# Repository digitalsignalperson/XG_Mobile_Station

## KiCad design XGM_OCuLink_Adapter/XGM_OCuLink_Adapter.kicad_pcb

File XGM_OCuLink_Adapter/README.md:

XGM to OCuLink Adapter
======================
A 33 x 18 mm board that plugs straight into the XG Mobile port of an ROG Flow / ROG Ally and presents a standard OCuLink 4i (SFF-8612) host port, so any off-the-shelf OCuLink eGPU dock can be used with a normal OCuLink cable.

**Status: untested design, revision 0.1. Do not order boards before working through [Before you order](#before-you-order).** The schematic is complete and checked; the board layout depends on the dimensions of a connector that had to be estimated from photos.

| Top copper | Bottom copper |
|---|---|
|  |  |

The XGM plug solders onto the lower edge, the OCuLink receptacle sits top right, the MCU top left.

## How it works
The XGM port is PCIe x8 plus a handful of sideband signals plus a USB-C port ([pinout](../Docs/Connector.md)). OCuLink 4i is PCIe x4 plus reference clock and reset. So the adapter has three jobs:

1. **Pass lanes 0-3 and the reference clock straight through.** No AC coupling capacitors are needed: PCIe puts them at each transmitter, so they already exist on the laptop motherboard and on the graphics card. Lanes 4-7 are left open and the host trains the link down to x4.
2. **Answer the handshake.** The laptop's embedded controller will not switch the PCIe mux over until a dock identifies itself over the sideband pins and the SMBus ([details](../Docs/MCU.md)). This is done by the same STM32F030C8T6, on the same pins, as the Lite dock, so the existing `XG_Mobile_Dock_MCU` firmware runs unmodified.
3. **Power itself.** OCuLink carries no power and there is no ATX supply here. A 5.1 kΩ resistor on CC1 makes the adapter look like a USB-C device, so the port's own USB-C half supplies 5 V on VBUS. A 3.3 V LDO feeds the MCU (about 10 mA).

`GPU_RST#` reaches the dock as OCuLink `PERST#` through the MCU, exactly as on the Lite dock. The other OCuLink sidebands (`CWAKE#`, `CPRSNT#`, the 2-wire bus, the 3.3 V / 5 V cable power pins) are not connected.

### About "you need redrivers"
A redriver is an amplifier that restores a PCIe signal which has been weakened by a long path. The comment that an adapter needs them assumed the adapter sits at the end of the ASUS XGM cable, so the signal would cross that cable *and* an OCuLink cable. This design removes the ASUS cable entirely: the plug is soldered to the board and the trace length from plug to OCuLink connector is about 10 mm. The signal path is laptop, 10 mm of board, one OCuLink cable, dock. That is comparable to the stock setup, so this revision is passive.

Expect PCIe 3.0 to work. PCIe 4.0 is plausible on a ROG Flow (which has redrivers on its motherboard) with a short, good cable, and less likely on a ROG Ally (which has none). If the link is unstable, use a shorter cable or let it fall back to 3.0, see the troubleshooting section of the [main README](../README.md).

## The connector problem
The male XGM plug is not a catalogue part. Parts stores only sell the receptacle that sits in the laptop. The only source is an ASUS XG Mobile cable ([part 14017-00810700](https://www.a-accessories.com/asus-connection-cable-62505-79153.htm), about $129, or a cable from a dead XG Mobile): open the cable head and desolder the plug from the small PCB inside. [These photos](../Docs/Diary.md#pin-mapping) show what that PCB looks like. The plug straddles the board edge, with rows A and C soldered on one face and rows B and D on the other.

Because of that, the plug footprint (`lib/XGM_OCuLink.pretty/XGM_Plug_Straddle.kicad_mod`) is an **estimate** made from those photos. The values that were guessed are at the top of `gen/make_fp.py`:

| Parameter  | Guess   | Meaning                                         |
|------------|---------|-------------------------------------------------|
| `pitch`    | 0.5 mm  | contact pitch, both sections                    |
| `pad_w`    | 0.28 mm | solder pad width                                |
| `pad_len`  | 1.4 mm  | solder pad length                               |
| `pad_edge` | 0.3 mm  | board edge to start of pad                      |
| `usb_gap`  | 4.1 mm  | centre of C31 to centre of A1                   |
| `shell_*`  |         | size and position of the shell tabs             |
| `board_t`  | 0.8 mm  | PCB thickness the plug is made to straddle      |

The outline of the board around the plug (notches for the plastic posts visible in the photos) is not modelled at all.

## Before you order
1. Get the plug. Measure it and the original cable-head PCB with calipers: every value in the table above, plus the cut-outs in the board edge.
2. Confirm with a multimeter that row D sits under row C with the same numbering (D1 under C1) and that B12 sits under A1. The original PCB has these labels on its silkscreen.
3. Put the measured values into `gen/make_fp.py` and regenerate (see below). The PCIe routing is computed from these numbers and follows them. Add the edge cut-outs in KiCad.
4. Check the chosen OCuLink receptacle against the footprint. It was drawn for the Amphenol G14A421211112HR; other SFF-8612 right-angle receptacles differ.
5. Enter the stack-up of your PCB fab into its impedance calculator and adjust `W_PAIR` / `GAP_PAIR` in `gen/make_pcb.py` for 85 Ω differential. The current 0.16 mm / 0.15 mm is an approximation for a 0.1 mm prepreg (JLC04081H-3313).
6. Run DRC in KiCad.

Things that can only be found out with a board in hand:

* Whether the port supplies VBUS early enough at boot for the MCU to answer the BIOS check. The `5V` pad (TP7) accepts external 5 V if it does not.
* Whether the plug stays seated. The original cable head latches into the laptop; this board is held by friction and the solder joints of the plug shell, with a stiff OCuLink cable hanging off it. A printed shell is advisable.
* Whether your dock powers the GPU up on its own. Docks that expect 3.3 V on the OCuLink cable power pins to switch on will need their manual power switch.

## Using it
Flash `XG_Mobile_Dock_MCU.bin` through the row of pads on the bottom side (`DIO`, `CLK`, `GND`, `3V3`), as described in the [main README](../README.md#stm32-mcu). `TX` is the debug log at 115200 baud.

The firmware's cable-lock input is left floating, which reads as "locked", so the adapter announces itself as soon as it is plugged in. Bridging `JP1` reads as "unlocked".

* White LED: connected and locked. Red LED: the host has enabled the eGPU.
* Windows: install [XGMDriver](../README.md#install-xgmdriver).
* Linux: the `asus-nb-wmi` driver exposes `egpu_enable` under `/sys/devices/platform/asus-nb-wmi/` (also reachable through `asusctl`). Write `1` to it after plugging in, then reboot or rescan the PCI bus.
* The USB-C half of the port is used up by the adapter. A ROG Flow can charge from its other USB-C port; a first-generation ROG Ally has no other port and cannot charge while the adapter is in.

## Files
| Path                                | Contents                                                  |
|-------------------------------------|-----------------------------------------------------------|
| `XGM_OCuLink_Adapter.kicad_sch`     | Schematic (generated: every pin carries a net label)      |
| `XGM_OCuLink_Adapter.kicad_pcb`     | 4-layer board, 0.8 mm, inner layers are solid ground      |
| `lib/`                              | Symbols and footprints used by the project                |
| `gen/design.py`                     | Parts, pins and nets. The single source of truth          |
| `gen/make_fp.py`                    | Plug footprint, with the estimated dimensions             |
| `gen/make_sch.py`                   | Writes the symbol library and the schematic               |
| `gen/make_pcb.py`, `gen/router.py`  | Placement, PCIe routing by construction, low-speed router |

To regenerate everything (KiCad 9 or later, with its Python module, numpy and scipy):

```
cd gen
./make_fp.py && ./make_sch.py
kicad-cli sch export netlist --format kicadsexpr -o /tmp/adapter.net ../XGM_OCuLink_Adapter.kicad_sch
./make_pcb.py /tmp/adapter.net      # takes about two minutes
```

The PCIe pairs are placed by formula, so their geometry is exact and repeatable. The low-speed nets are placed by a simple grid router: they are electrically correct and pass DRC, but they are not pretty, and are worth tidying by hand once the footprint is final.

## Layout notes
* TX pairs run on the top layer from plug row C to OCuLink row B. RX pairs drop to the bottom layer, pass under row B and come back up between the two pad rows to reach row A. Every ground pin next to a pair has its own via into the planes, at both connectors.
* Polarity and lane order are preserved end to end.
* The reference clock starts on the bottom face (row D) and has to cross lane 2 to reach the middle of the OCuLink connector. It does so on the bottom layer while RX2 is still on the top layer, so no pair crosses a gap in its ground plane.
* `PERST#` runs around the front of the OCuLink connector instead of across the pairs.

## Sources
* OCuLink pin assignment: SFF-9402 Rev 1.1, Table 7-1, root side.
* OCuLink footprint: Antmicro [oculink-pcie-adapter](https://github.com/antmicro/oculink-pcie-adapter) (Apache-2.0).

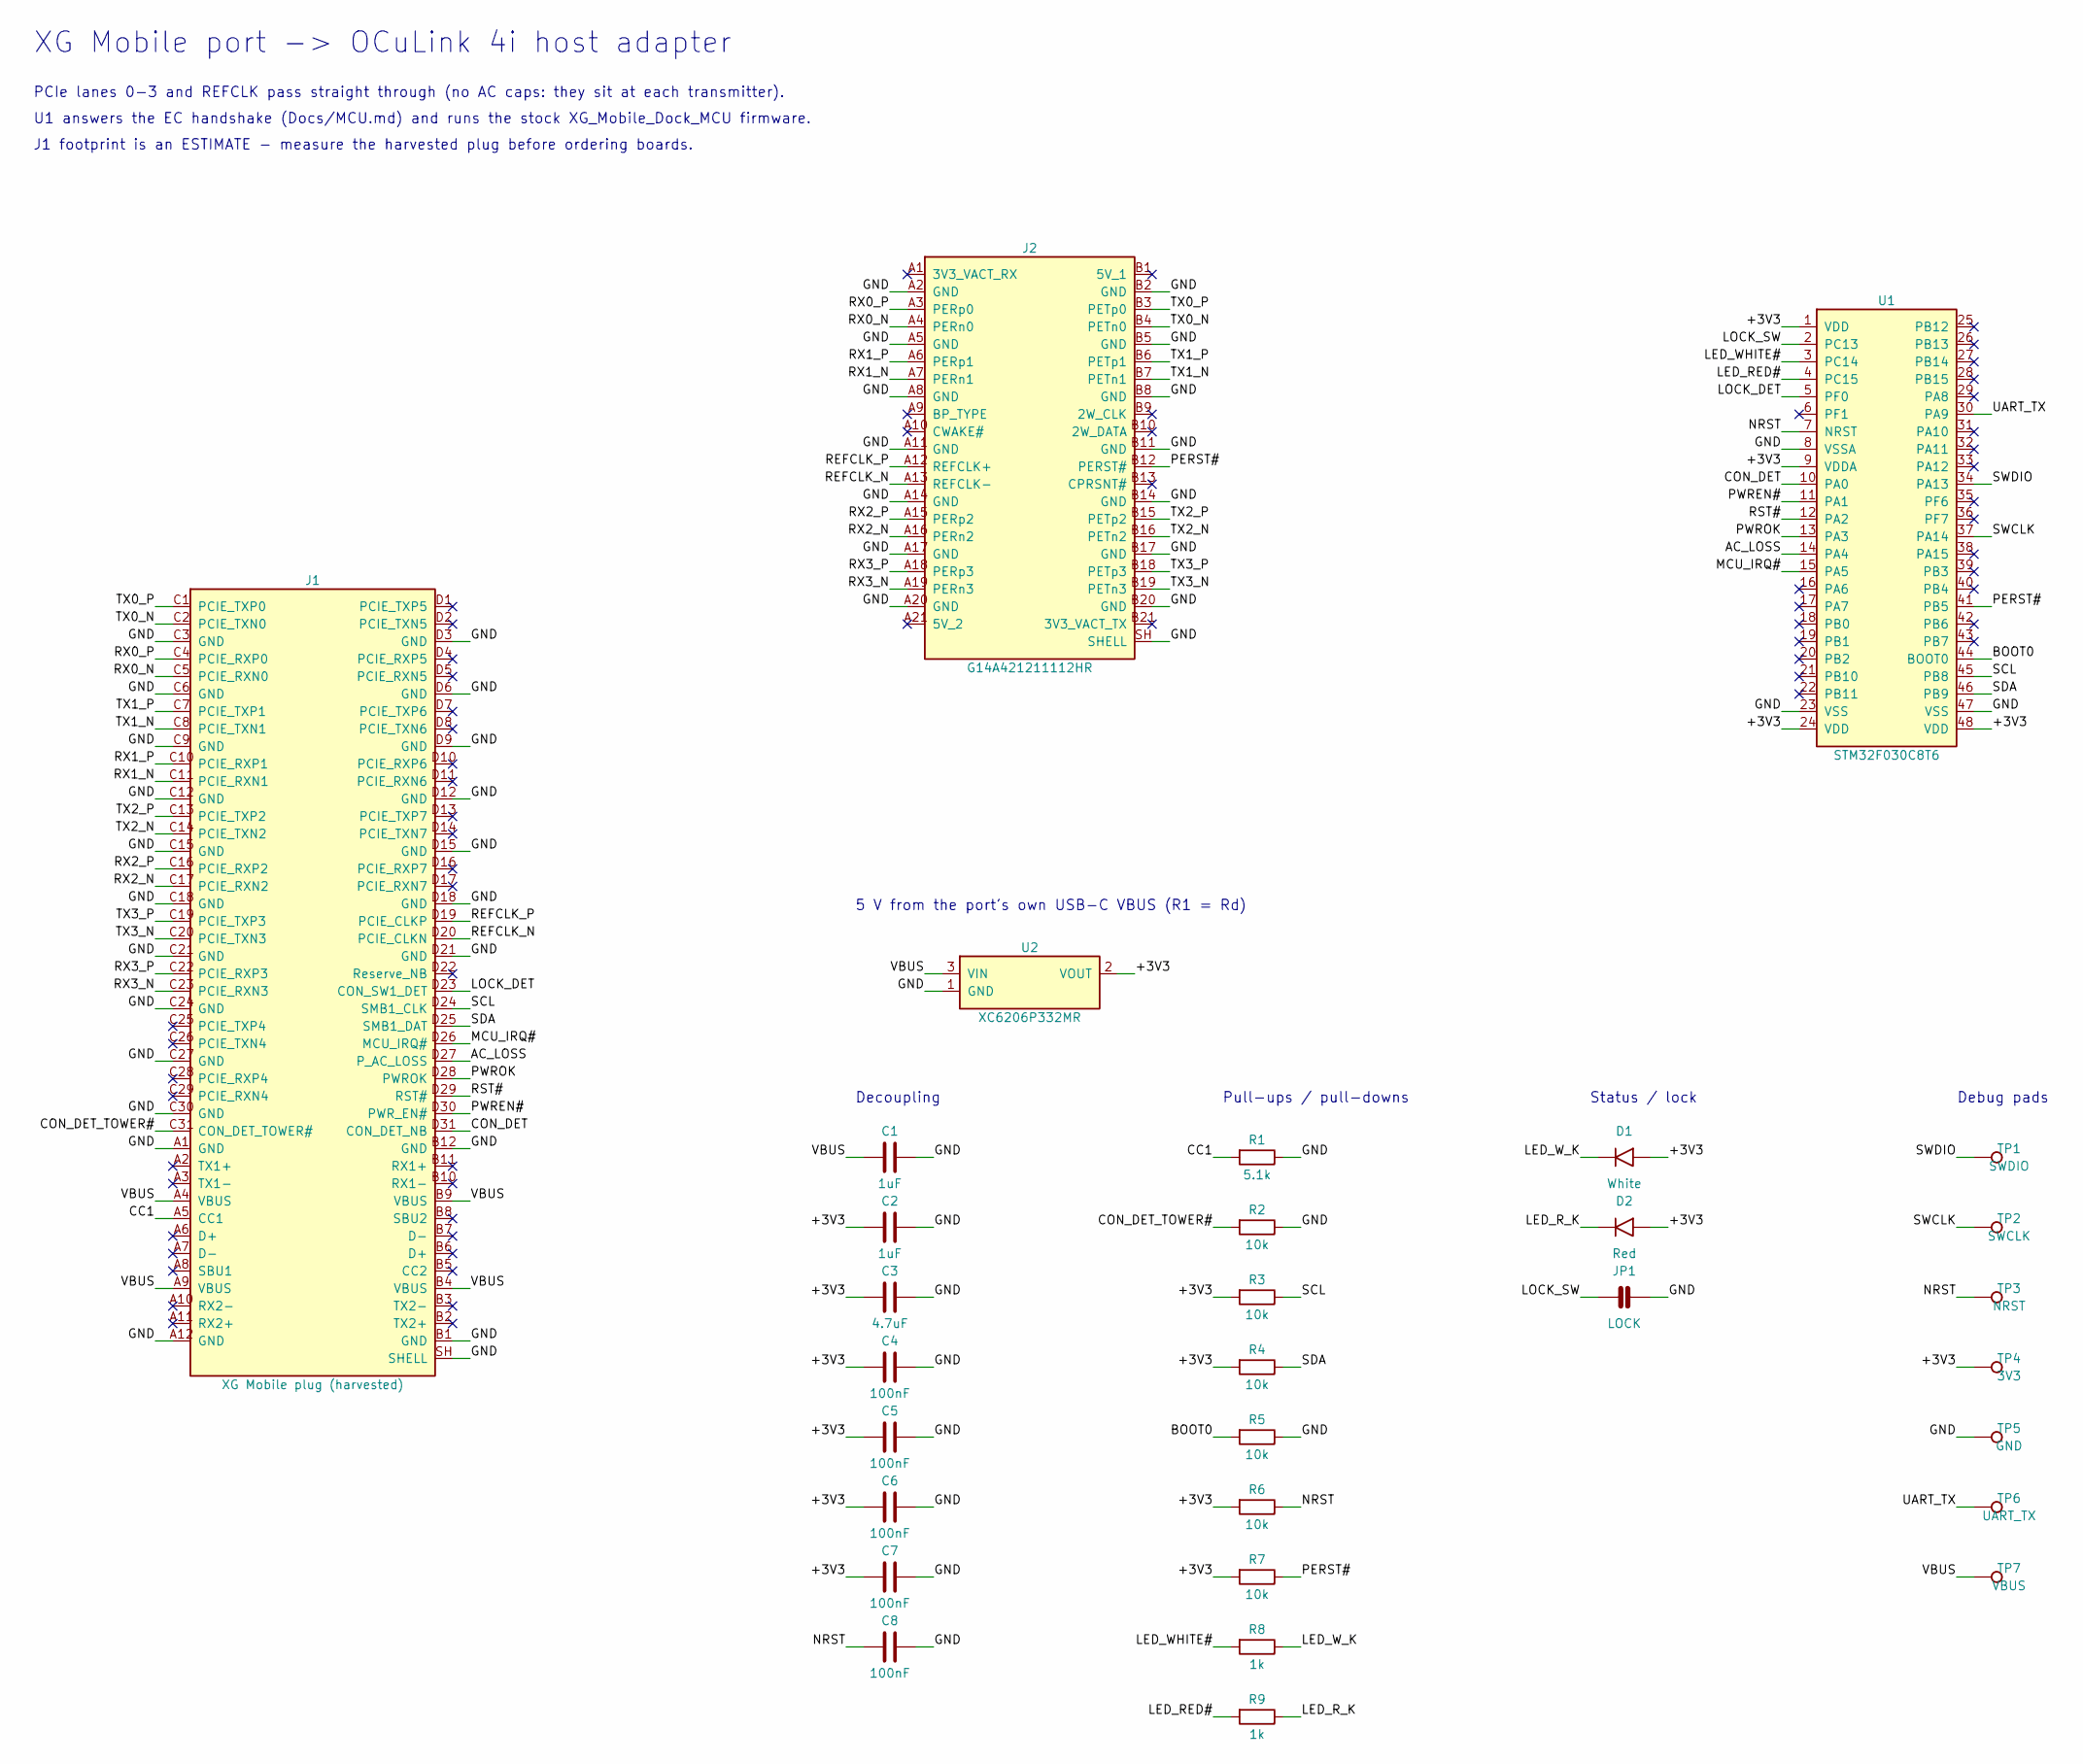
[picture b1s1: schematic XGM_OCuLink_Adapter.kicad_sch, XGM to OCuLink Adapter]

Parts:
C1, C2: 1uF; C_0402_1005Metric; LCSC C52923
C3: 4.7uF; C_0402_1005Metric; LCSC C23733
C4, C5, C6, C7, C8: 100nF; C_0402_1005Metric; LCSC C1525
D1: White; LED_0603_1608Metric; LCSC C2290
D2: Red; LED_0603_1608Metric; LCSC C2286
J1: XG Mobile plug (harvested); XGM_Plug_Straddle
J2: G14A421211112HR; Amphenol_G14A421211112HR
JP1: LOCK; SolderJumper_2_Open
R1: 5.1k; R_0402_1005Metric; LCSC C25905
R2, R3, R4, R5, R6, R7: 10k; R_0402_1005Metric; LCSC C25744
R8, R9: 1k; R_0402_1005Metric; LCSC C11702
TP1: SWDIO; TestPoint_Pad_D1.0mm
TP2: SWCLK; TestPoint_Pad_D1.0mm
TP3: NRST; TestPoint_Pad_D1.0mm
TP4: 3V3; TestPoint_Pad_D1.0mm
TP5: GND; TestPoint_Pad_D1.0mm
TP6: UART_TX; TestPoint_Pad_D1.0mm
TP7: VBUS; TestPoint_Pad_D1.0mm
U1: STM32F030C8T6; LQFP-48_7x7mm_P0.5mm; LCSC C23922
U2: XC6206P332MR; SOT-23; LCSC C5446

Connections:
/+3V3: C2.1, C3.1, C4.1, C5.1, C6.1, C7.1, D1.2 (A), D2.2 (A), R3.1, R4.1, R6.1, R7.1, TP4.1, U1.1 (VDD), U1.9 (VDDA), U1.24 (VDD), U1.48 (VDD), U2.2 (VOUT)
/AC_LOSS: J1.D27 (P_AC_LOSS), U1.14 (PA4)
/BOOT0: R5.1, U1.44 (BOOT0)
/CC1: J1.A5 (CC1), R1.1
/CON_DET: J1.D31 (CON_DET_NB), U1.10 (PA0)
/CON_DET_TOWER#: J1.C31 (CON_DET_TOWER#), R2.1
/GND: C1.2, C2.2, C3.2, C4.2, C5.2, C6.2, C7.2, C8.2, J1.A1 (GND), J1.A12 (GND), J1.B1 (GND), J1.B12 (GND), J1.C3 (GND), J1.C6 (GND), J1.C9 (GND), J1.C12 (GND), J1.C15 (GND), J1.C18 (GND), J1.C21 (GND), J1.C24 (GND), J1.C27 (GND), J1.C30 (GND), J1.D3 (GND), J1.D6 (GND), J1.D9 (GND), J1.D12 (GND), J1.D15 (GND), J1.D18 (GND), J1.D21 (GND), J1.SH (SHELL), J2.A2 (GND), J2.A5 (GND), J2.A8 (GND), J2.A11 (GND), J2.A14 (GND), J2.A17 (GND), J2.A20 (GND), J2.B2 (GND), J2.B5 (GND), J2.B8 (GND), J2.B11 (GND), J2.B14 (GND), J2.B17 (GND), J2.B20 (GND), J2.SH (SHELL), JP1.2 (B), R1.2, R2.2, R5.2, TP5.1, U1.8 (VSSA), U1.23 (VSS), U1.47 (VSS), U2.1 (GND)
/LED_RED#: R9.1, U1.4 (PC15)
/LED_R_K: D2.1 (K), R9.2
/LED_WHITE#: R8.1, U1.3 (PC14)
/LED_W_K: D1.1 (K), R8.2
/LOCK_DET: J1.D23 (CON_SW1_DET), U1.5 (PF0)
/LOCK_SW: JP1.1 (A), U1.2 (PC13)
/MCU_IRQ#: J1.D26 (MCU_IRQ#), U1.15 (PA5)
/NRST: C8.1, R6.2, TP3.1, U1.7 (NRST)
/PERST#: J2.B12 (PERST#), R7.2, U1.41 (PB5)
/PWREN#: J1.D30 (PWR_EN#), U1.11 (PA1)
/PWROK: J1.D28 (PWROK), U1.13 (PA3)
/REFCLK_N: J1.D20 (PCIE_CLKN), J2.A13 (REFCLK-)
/REFCLK_P: J1.D19 (PCIE_CLKP), J2.A12 (REFCLK+)
/RST#: J1.D29 (RST#), U1.12 (PA2)
/RX0_N: J1.C5 (PCIE_RXN0), J2.A4 (PERn0)
/RX0_P: J1.C4 (PCIE_RXP0), J2.A3 (PERp0)
/RX1_N: J1.C11 (PCIE_RXN1), J2.A7 (PERn1)
/RX1_P: J1.C10 (PCIE_RXP1), J2.A6 (PERp1)
/RX2_N: J1.C17 (PCIE_RXN2), J2.A16 (PERn2)
/RX2_P: J1.C16 (PCIE_RXP2), J2.A15 (PERp2)
/RX3_N: J1.C23 (PCIE_RXN3), J2.A19 (PERn3)
/RX3_P: J1.C22 (PCIE_RXP3), J2.A18 (PERp3)
/SCL: J1.D24 (SMB1_CLK), R3.2, U1.45 (PB8)
/SDA: J1.D25 (SMB1_DAT), R4.2, U1.46 (PB9)
/SWCLK: TP2.1, U1.37 (PA14)
/SWDIO: TP1.1, U1.34 (PA13)
/TX0_N: J1.C2 (PCIE_TXN0), J2.B4 (PETn0)
/TX0_P: J1.C1 (PCIE_TXP0), J2.B3 (PETp0)
/TX1_N: J1.C8 (PCIE_TXN1), J2.B7 (PETn1)
/TX1_P: J1.C7 (PCIE_TXP1), J2.B6 (PETp1)
/TX2_N: J1.C14 (PCIE_TXN2), J2.B16 (PETn2)
/TX2_P: J1.C13 (PCIE_TXP2), J2.B15 (PETp2)
/TX3_N: J1.C20 (PCIE_TXN3), J2.B19 (PETn3)
/TX3_P: J1.C19 (PCIE_TXP3), J2.B18 (PETp3)
/UART_TX: TP6.1, U1.30 (PA9)
/VBUS: C1.1, J1.A4 (VBUS), J1.A9 (VBUS), J1.B4 (VBUS), J1.B9 (VBUS), TP7.1, U2.3 (VIN)

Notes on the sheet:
XG Mobile port -> OCuLink 4i host adapter
PCIe lanes 0-3 and REFCLK pass straight through (no AC caps: they sit at each transmitter).
U1 answers the EC handshake (Docs/MCU.md) and runs the stock XG_Mobile_Dock_MCU firmware.
J1 footprint is an ESTIMATE - measure the harvested plug before ordering boards.
5 V from the port's own USB-C VBUS (R1 = Rd)
Decoupling
Pull-ups / pull-downs
Status / lock
Debug pads

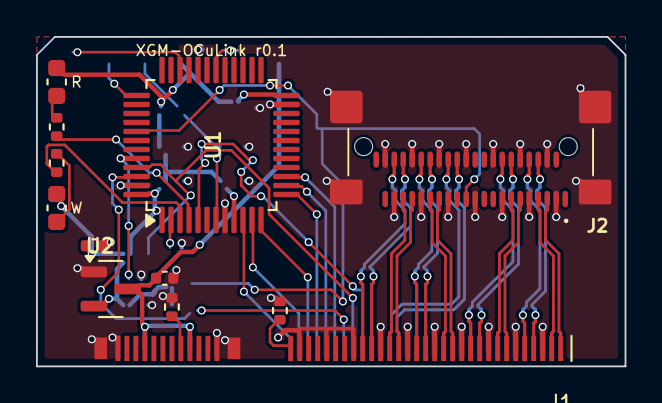
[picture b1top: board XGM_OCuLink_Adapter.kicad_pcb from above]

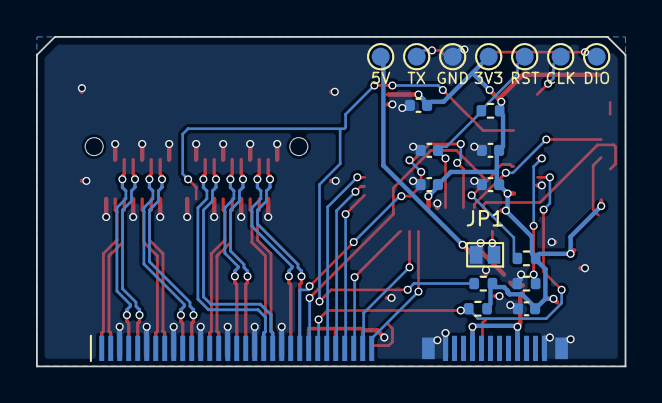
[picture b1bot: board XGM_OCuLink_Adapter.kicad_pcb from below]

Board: 4 copper layers, 32.7 x 18.3 mm, 31 parts (19 on the bottom side), 43 nets.

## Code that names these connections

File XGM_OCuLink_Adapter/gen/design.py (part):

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# STM32F030C8T6, same pin use as the Lite dock (stock firmware compatible)
# --------------------------------------------------------------------------
MCU_PINS = [
    (1, "VDD", "+3V3"), (2, "PC13", "LOCK_SW"), (3, "PC14", "LED_WHITE#"),
    (4, "PC15", "LED_RED#"), (5, "PF0", "LOCK_DET"), (6, "PF1", None),
    (7, "NRST", "NRST"), (8, "VSSA", "GND"), (9, "VDDA", "+3V3"),
    (10, "PA0", "CON_DET"), (11, "PA1", "PWREN#"), (12, "PA2", "RST#"),
    (13, "PA3", "PWROK"), (14, "PA4", "AC_LOSS"), (15, "PA5", "MCU_IRQ#"),
    (16, "PA6", None), (17, "PA7", None), (18, "PB0", None),
    (19, "PB1", None), (20, "PB2", None), (21, "PB10", None),
    (22, "PB11", None), (23, "VSS", "GND"), (24, "VDD", "+3V3"),
    (25, "PB12", None), (26, "PB13", None), (27, "PB14", None),
    (28, "PB15", None), (29, "PA8", None), (30, "PA9", "UART_TX"),
    (31, "PA10", None), (32, "PA11", None), (33, "PA12", None),
    (34, "PA13", "SWDIO"), (35, "PF6", None), (36, "PF7", None),
    (37, "PA14", "SWCLK"), (38, "PA15", None), (39, "PB3", None),
    (40, "PB4", None), (41, "PB5", "PERST#"), (42, "PB6", None),
    (43, "PB7", None), (44, "BOOT0", "BOOT0"), (45, "PB8", "SCL"),
    (46, "PB9", "SDA"), (47, "VSS", "GND"), (48, "VDD", "+3V3"),
]

# --------------------------------------------------------------------------
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

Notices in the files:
parts and their libraries:
License: Apache-2.0
